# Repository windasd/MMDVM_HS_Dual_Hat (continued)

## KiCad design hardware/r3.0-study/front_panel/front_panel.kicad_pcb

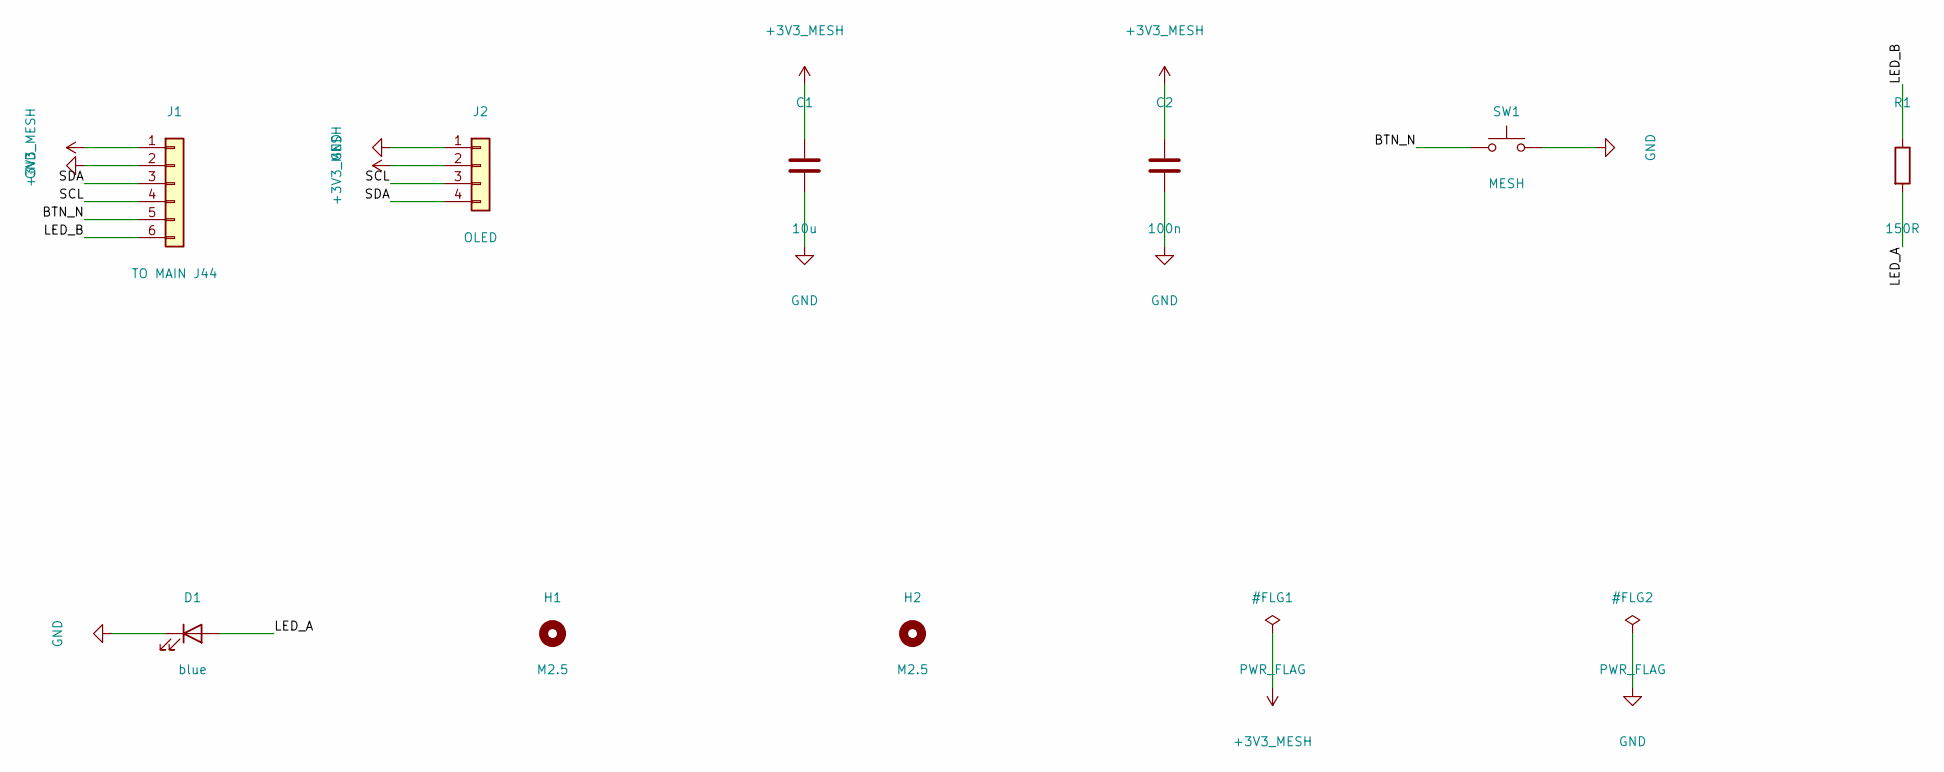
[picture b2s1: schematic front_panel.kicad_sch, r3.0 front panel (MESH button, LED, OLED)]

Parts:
C1: 10u; C_0603_1608Metric; MPN CL10A106MA8NRNC; Mouser 187-CL10A106MA8NRNC
C2: 100n; C_0402_1005Metric; MPN CL05B104KO5NNNC; Mouser 187-CL05B104KO5NNNC
D1: blue; LED_0805_2012Metric; MPN APT2012QBC/D; Mouser 604-APT2012QBC/D
H1, H2: M2.5; MountingHole_2.7mm_M2.5
J1: TO MAIN J44; JST_SH_SM06B-SRSS-TB_1x06-1MP_P1.00mm_Horizontal; MPN SM06B-SRSS-TB(LF)(SN); Mouser 306-M06BSRSSTBLFSNPP
J2: OLED; PinHeader_1x04_P2.54mm_Vertical; MPN 61300411121; Mouser 710-61300411121
R1: 150R; R_0402_1005Metric; MPN 0402WGF1500TCE; Mouser 303-0402WGF1500TCE
SW1: MESH; SW_PUSH_6mm_H8mm; MPN TS02-66-80-BK-260-LCR-D; Mouser 179-TS026680BK260LCR

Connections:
+3V3_MESH: C1.1, C2.1, J1.1, J2.2
/BTN_N: J1.5, SW1.1
/LED_A: D1.2 (A), R1.2
/LED_B: J1.6, R1.1
/SCL: J1.4, J2.3
/SDA: J1.3, J2.4
GND: C1.2, C2.2, D1.1 (K), J1.2, J2.1, SW1.2

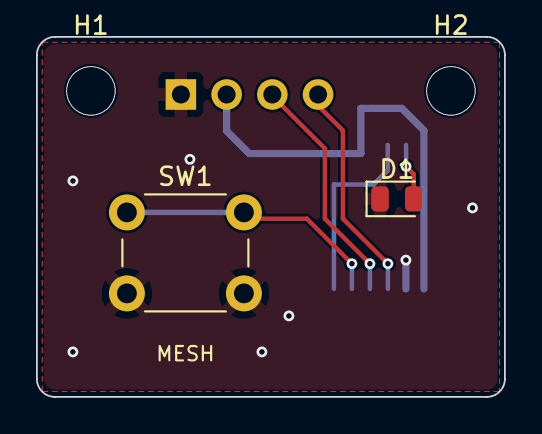
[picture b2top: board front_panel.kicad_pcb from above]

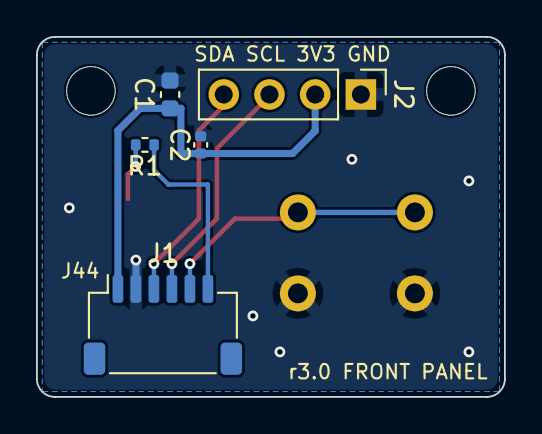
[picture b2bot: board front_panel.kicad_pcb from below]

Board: 2 copper layers, 26.0 x 20.0 mm, 9 parts (5 on the bottom side), 7 nets.

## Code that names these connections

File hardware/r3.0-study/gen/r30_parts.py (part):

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                                                                '4': '+5V'},
          'Connector_JST:JST_XH_B4B-XH-A_1x04_P2.50mm_Vertical',
          {'MPN': 'JST B4B-XH-A', 'Note': 'pin order = TJC XH (1 GND, 2 RX, 3 TX, 4 5V): use a 1:1 cable'}),
        R('R32', '1k', 'DISP_TX5V', 'DISP_RXD', Note='TJC X5 TX is 5 V, PA3 is not 5 V tolerant'),
        C('C53', '10u', '+5V', 'GND', FP_C0805),
        # STM32 USB pins (PA11/PA12) are unused on this board: test pads only
        P('TP3', 'Connector:TestPoint', 'D-', {'1': 'D-'}, 'TestPoint:TestPoint_Pad_D1.0mm', in_bom=False),
        P('TP4', 'Connector:TestPoint', 'D+', {'1': 'D+'}, 'TestPoint:TestPoint_Pad_D1.0mm', in_bom=False),
    ]
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    ls = {'1': 'GND', '2': 'GND', '3': None, '4': 'HOST_PWR_BTN_N', '5': 'LS_UART0_TX', '6': 'HOST_RST_BTN_N',
          '7': 'LS_UART0_RX', '8': None, '9': None, '10': None, '11': 'LS_CON_TX', '12': None, '13': 'LS_CON_RX',
          '14': None, '15': 'LS_SCL', '16': None, '17': 'LS_SDA', '18': None, '19': None, '20': None, '21': None,
          '22': None, '23': 'LS_GPIO_A', '24': 'LS_GPIO_B', '25': 'LS_GPIO_C', '26': 'LS_GPIO_D',
          '27': 'LS_GPIO_E', '28': 'LS_GPIO_F', '29': 'LS_GPIO_G', '30': 'LS_GPIO_H', '31': 'LS_GPIO_I',
          '32': 'LS_GPIO_J', '33': None, '34': None, '35': '+1V8_HOST', '36': 'SYS_DCIN', '37': None,
          '38': 'SYS_DCIN', '39': 'GND', '40': 'GND'}
    p = [
        P('J1', 'Connector_Generic:Conn_02x20_Odd_Even', '96Boards LS', ls,
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        # MMDVM host UART (STM32 USART1)
        LVC1T45('U20', '+1V8_HOST', '+3V3', 'LS_UART0_RX', 'TXD', False, 'STM32 TX -> host UART0 RX'),
        LVC1T45('U21', '+1V8_HOST', '+3V3', 'LS_UART0_TX', 'RXD', True, 'host UART0 TX -> STM32 RX'),
        LVC1T45('U22', '+1V8_HOST', '+3V3', 'LS_GPIO_A', 'HOST_BOOT0', True, 'GPIO-A -> STM32 BOOT0 (via R25)'),
        OD_BUF('U23', '+1V8_HOST', 'LS_GPIO_B', 'NRST', 'GPIO-B low -> STM32 NRST low (open drain)'),
        # The host GPIOs are inputs until software configures them. Without these the buffer inputs float once
        # +1V8 is up: the STM32 could be held in reset or start in its boot loader.
        R('R57', '100k', 'LS_GPIO_A', 'GND', Note='BOOT0 request low until the host drives GPIO-A'),
        R('R58', '100k', 'LS_GPIO_B', '+1V8_HOST', Note='no STM32 reset until the host drives GPIO-B'),
        # console (UART1 = ttyOWL5) to the side-panel header, FTDI pin order
        LVC1T45('U24', '+1V8_HOST', '+3V3', 'LS_CON_TX', 'CON_RXD_B', True, 'host console TX -> PC'),
        LVC1T45('U25', '+1V8_HOST', '+3V3', 'LS_CON_RX', 'CON_TXD_B', False, 'PC -> host console RX'),
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          'MMDVM_r30:PinHeader_1x06_P2.54mm_Horizontal_EdgeMount',
          {'Note': 'FTDI TTL-232R-3V3 order: 1 GND, 2 CTS nc, 3 VCC nc, 4 TXD in, 5 RXD out, 6 RTS nc'}),
        # Meshtastic MCU reset, GPS PPS and GPS switch state
        OD_BUF('U26', '+1V8_HOST', 'LS_GPIO_G', 'MESH_RST_N', 'GPIO-G low -> RAK4630 reset'),
        R('R59', '100k', 'LS_GPIO_G', '+1V8_HOST',
          Note='the always-on RAK4630 must not be reset while the host boots (GPIO-G floating)'),
        LVC1T45('U27', '+1V8_HOST', '+3V3_MESH', 'LS_GPIO_H', 'GPS_PPS', False, 'GPS PPS -> GPIO-H (pps-gpio)'),
        LVC1T45('U28', '+1V8_HOST', '+3V3_MESH', 'LS_GPIO_I', 'GPS_ON', False, 'GPS switch -> GPIO-I'),
        # power-hold: JP2 selects +1V8 present (default) or GPIO-F (gpio-poweroff, active low)
        P('JP2', 'Jumper:SolderJumper_3_Bridged12', 'HOLD_SRC', {'1': '+1V8_HOST', '2': 'HOLD_A', '3': 'LS_GPIO_F'},
          'Jumper:SolderJumper-3_P1.3mm_Bridged12_RoundedPad1.0x1.5mm',
          {'Note': '1-2: hold while +1V8 present (default); 2-3: hold = GPIO-F (gpio-poweroff active-low)'},
          in_bom=False),
        LVC1T45('U29', '+1V8_HOST', '+3V3_MESH', 'HOLD_A', 'HOST_HOLD', True, 'host alive -> STM6601 PS_HOLD'),
        R('R125', '100k', 'LS_GPIO_F', '+1V8_HOST',
          Note='with JP2 at 2-3: hold stays high until gpio-poweroff drives GPIO-F low (and across a reboot)'),
        R('R43', '100k', 'HOST_HOLD', 'GND', Note='low when the host is unpowered (Ioff)'),
        # open-drain status lines into host GPIOs (1.8 V pull-ups)
        OD_BUF('U30', '+1V8_HOST', 'SC16_IRQ_N', 'LS_GPIO_C', 'SC16IS752 IRQ -> GPIO-C'),
        OD_BUF('U31', '+1V8_HOST', 'PWR_INT_N', 'LS_GPIO_D', 'charger INT / gauge ALRT -> GPIO-D'),
        OD_BUF('U32', '+1V8_HOST', 'BTN_INT_N', 'LS_GPIO_E', 'power-button request -> GPIO-E'),
        OD_BUF('U33', '+1V8_HOST', 'FAN_ALERT_N', 'LS_GPIO_J', 'fan controller ALERT -> GPIO-J'),
        R('R44', '10k', 'LS_GPIO_C', '+1V8_HOST'), R('R45', '10k', 'LS_GPIO_D', '+1V8_HOST'),
        R('R46', '10k', 'LS_GPIO_E', '+1V8_HOST'), R('R47', '10k', 'LS_GPIO_J', '+1V8_HOST'),
        # TI logic datasheets (SN74LVC1T45, SN74LVC1G07): a 0.1 uF bypass capacitor at every VCC pin. Added
        # 2026-11-26; until then the 14 translators / buffers shared C60 on +1V8_HOST only.
        C('C187', '100n', '+1V8_HOST', 'GND', Note='U20 VCCA'), C('C188', '100n', '+3V3', 'GND', Note='U20 VCCB'),
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
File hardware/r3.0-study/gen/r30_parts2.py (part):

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        '9': 'MESH_API_RX', '10': 'MESH_API_TX',                # P0.19 / P0.20: serial module (PROTO) to the host
        '11': None,                                             # P0.21: buzzer PWM (not fitted)
        '12': None,                                             # P0.10: AQ_SET, driven high by the firmware
        '13': 'MESH_BTN_N',                                     # P0.09: user button (needs UICR NFCPINS = GPIO)
        '14': 'GND', '15': 'MESH_RF_BT', '16': 'GND',
        '17': 'MESH_RST_N', '18': 'MESH_SWDCLK', '19': 'MESH_SWDIO',
        '20': '+3V3_MESH', '21': '+3V3_MESH', '22': 'GND',
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        C('C103', '10u', 'BQ_PMID', 'GND', FP_C0805, Note='25 V'), C('C104', '10u', 'BQ_PMID', 'GND', FP_C0805),
        # TI layout list (SLUSC88C 11.1, item 1): the input capacitor as close as possible to PMID and GND. C145 sits at
        # pin 23 with a ground via to In1; C103 / C104 stay as bulk.
        C('C145', '1u', 'BQ_PMID', 'GND', Note='25 V; BQ25895 PMID, next to pin 23'),
        C('C105', '47n', 'BQ_BTST', 'BQ_SW'), C('C106', '4u7', 'REGN', 'GND', FP_C0603),
        P('L100', 'Device:L', '1uH', {'1': 'BQ_SW', '2': 'VSYS'}, 'Inductor_SMD:L_Wuerth_HCI-5040',
          {'MPN': 'Wurth 7443340100 (1 uH, >7 A)'}),
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        # BT101 contact is under it on B.Cu), so C149 sits by pin 3 with a via to In1 and pin 1 has its own via.
        C('C149', '4u7', '+5V', 'GND', Note='10 V; TPS61022 VOUT, next to pin 3'),
        # TPS61022 input capacitor close to VIN and GND (SLVSDX7D 10.1); the nearest one was C143, 4.7 mm away
        C('C210', '4u7', 'VSYS', 'GND', Note='10 V; TPS61022 VIN, next to pins 6 / 7'),
        # ---- 3.5 V buck-boost (always on) -> LDOs
        P('U108', 'Regulator_Switching:TPS63030DSK', 'TPS63030', {
            '1': '+3V5', '2': 'BB_L2', '3': 'GND', '4': 'BB_L1', '5': 'VSYS', '6': 'VSYS', '7': 'VSYS',
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        C('C134', '10u', '+3V5', 'GND', FP_C0805),
        # TI layout guide (SLVS696D 11.1): input and output capacitors as close to the IC as possible. C143 / C144
        # sit at VIN (pin 5) and VOUT (pin 1) with their ground strapped to the PowerPAD; C132-C134 stay as bulk.
        C('C143', '10u', 'VSYS', 'GND', Note='TPS63030 VIN, next to pin 5'),
        C('C144', '10u', '+3V5', 'GND', Note='TPS63030 VOUT, next to pin 1'),
        P('U109', 'Regulator_Linear:TPS7A20xxxDBV', 'TPS7A2033', {'1': '+3V5', '2': 'GND', '3': '+3V5', '4': None,
                                                                  '5': '+3V3_MESH'},
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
